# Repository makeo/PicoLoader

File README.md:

# PicoLoader
This is an ODE-based modchip for the Nintendo GameCube to boot homebrew.\
Its price and functionality are very similar to [PicoBoot](https://github.com/webhdx/PicoBoot) but it has multiple advantages.

Join the [Discord server](https://discord.gg/YtA9aU3BKZ) to get support and discuss the mod!

## How does it work?
This mod works by emulating a disk drive during boot, executing a homebrew app, and afterwards re-enabling the disk drive.\
This is achieved using a flex PCB similar to FlippyDrive.
However, it is not a full optical drive emulator and only allows executing small homebrew apps (e.g. [swiss](https://github.com/emukidid/swiss-gc)) from flash just like PicoBoot.
To access files on an SD card, you need an SDGecko, SD2SP2, or similar adapter, which can be purchased separately.

## Features
- Open source
- You can keep the disk drive
- Simple to boot most homebrew apps using an [online converter](https://makeo.github.io/PicoLoader/converter/)
- No permanent modifications to the GameCube
- [3D printed plug](https://github.com/makeo/PicoLoader/raw/refs/heads/main/mount/Drive_PlugV1.1.stl) for installs without a disk drive 
- Easy to remove
- Running Pico at 200Mhz for better compatibility with clone boards

#### Soldered Variant
- Cheap and easy to get components (Raspberry Pi Pico/Pico 2 + Flex PCB + Diode)
- Readily available
- No soldering directly to the GameCube
- Easy soldering
- Alternative install options: [Panasonic Q](https://github.com/makeo/PicoLoader/wiki/4.-Advanced-Section#panasonic-q-install-option), [low-profile](https://github.com/makeo/PicoLoader/wiki/4.-Advanced-Section#low-profile-install-option)

#### Solderless Variant
- No soldering
- Easily replaceable flex PCB
- Pre-programmed with PicoLoader firmware and [Swiss](https://github.com/emukidid/swiss-gc)
> [!TIP]
> You can buy the solderless and normal variant from [store.makstech.io](https://store.makstech.io/).

## Planned Features
*cricked sound*

## Installation & Documentation
> [!IMPORTANT]
> Please follow the [installation instructions](https://makeo.github.io/PicoLoader/) in the wiki.\
> When not following the instructions, there is a chance of breaking the flex PCB during installation.

Get started by looking at the 📖[Wiki](https://github.com/makeo/PicoLoader/wiki/1.-Home)!

## Gallery

<div style="display: flex; gap: 10px; flex-wrap: nowrap; justify-content: center;">

</div>
<div style="display: flex; gap: 10px; flex-wrap: nowrap; justify-content: center;">

</div>

## Special Thanks
- [silversteel](https://github.com/silverstee1) for his help, especially for making the flex PCBs and mounts
- [TeamOffBroadway](https://github.com/OffBroadway) for the amazing idea to use a flex PCB to intercept the drive signals
- [Extrems](https://github.com/Extrems), [emukidid](https://github.com/emukidid) and everyone involved in creating Swiss
- [novenary (9ary)](https://github.com/9ary) for gekkoboot

## Acknowledgements
The source of [gbi.hdr](https://github.com/makeo/PicoLoader/blob/main/picoloader/data/gbi.hdr) and [gbi_disable_ipl.hdr](https://github.com/makeo/PicoLoader/blob/main/picoloader/data/gbi_disable_ipl.hdr) is licensed under GPL-2.0 and available [here](https://github.com/makeo/cubeboot-tools)

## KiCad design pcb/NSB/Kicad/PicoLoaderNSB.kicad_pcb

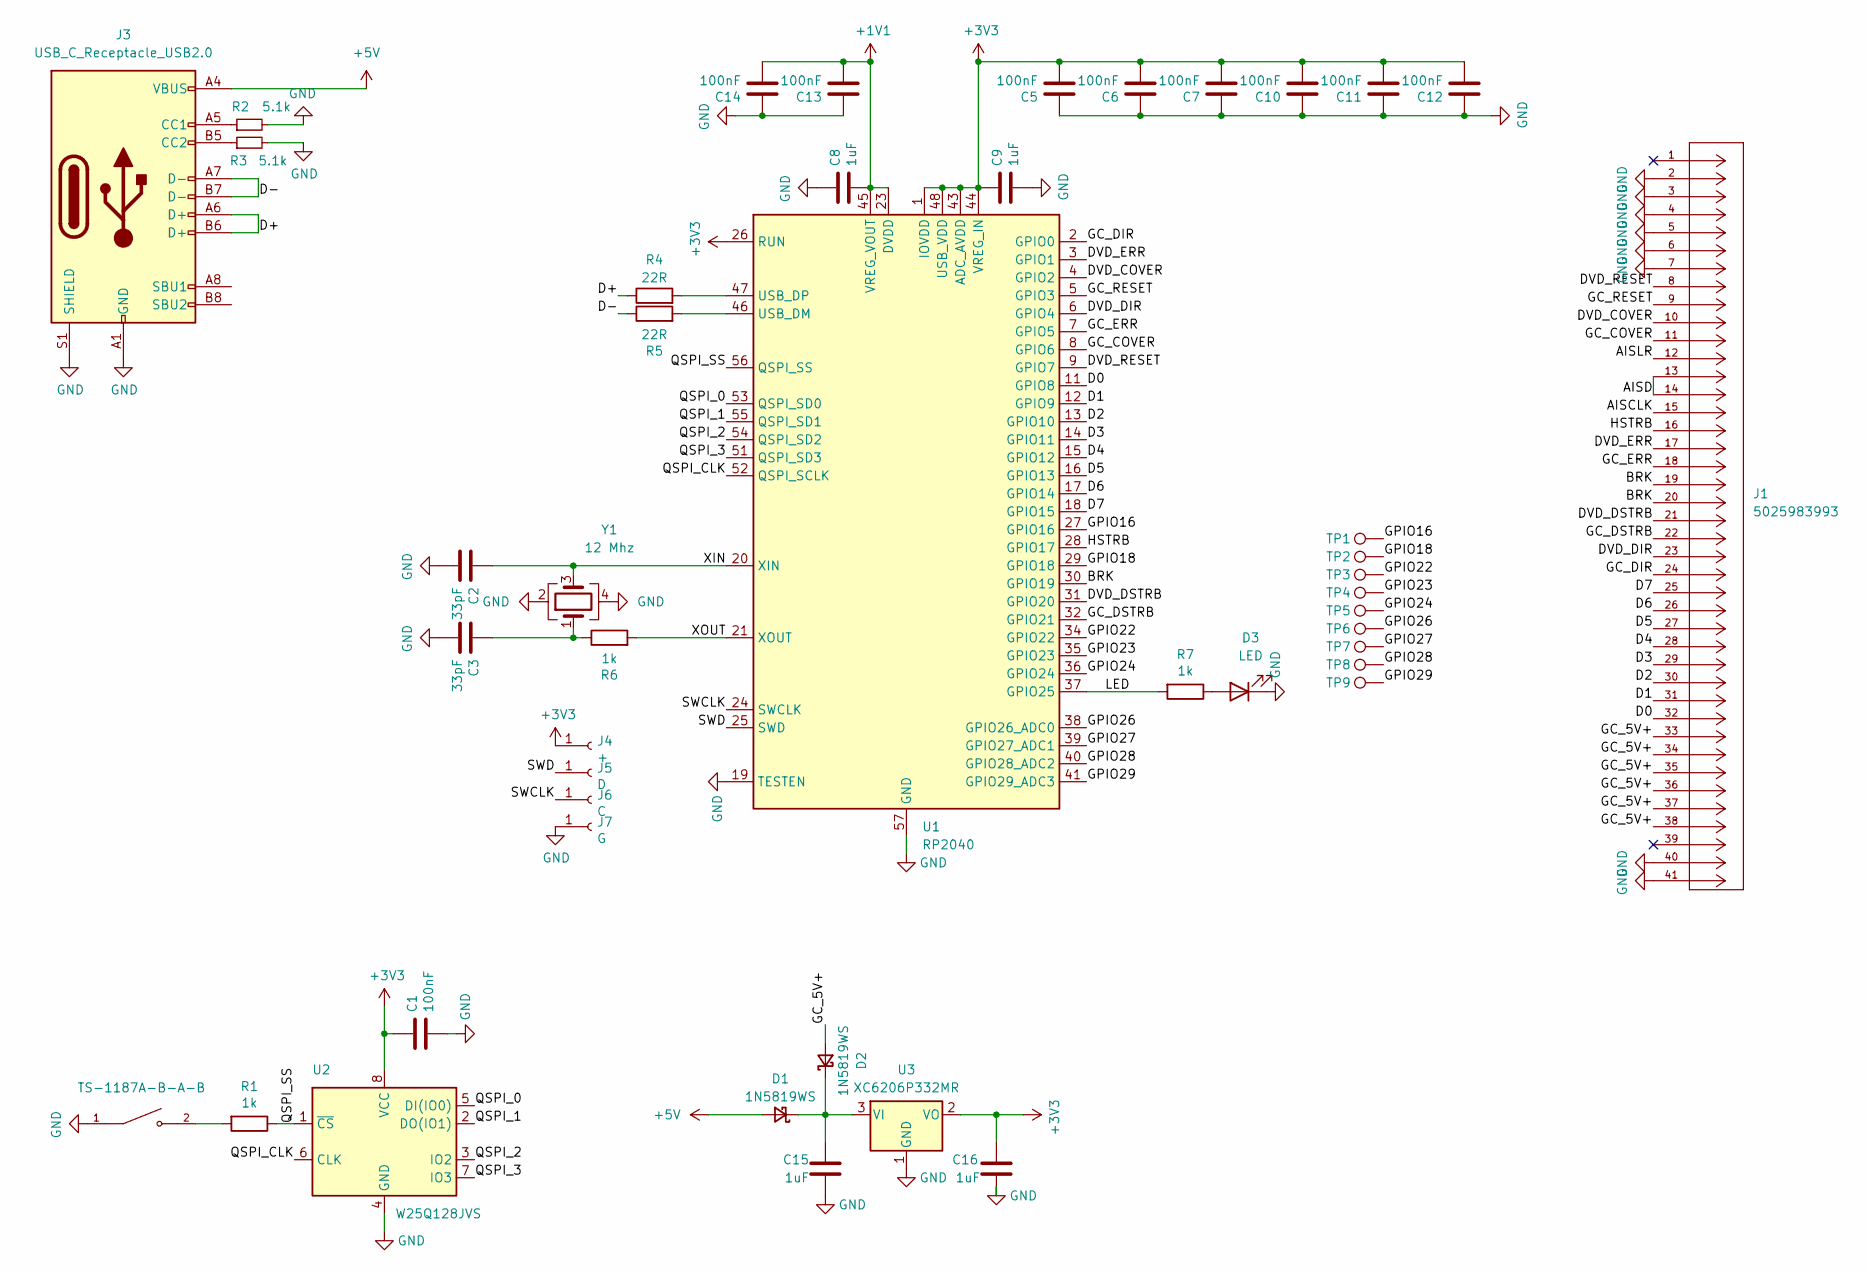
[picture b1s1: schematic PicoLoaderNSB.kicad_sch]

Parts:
C1, C5, C6, C7, C10, C11, C12, C13, C14: 100nF; C_0402_1005Metric; LCSC C1525
C2, C3: 33pF; C_0402_1005Metric; LCSC C1562
C8, C9, C15, C16: 1uF; C_0402_1005Metric; LCSC C52923
D1, D2: 1N5819WS; D_SOD-323; LCSC C191023
D3: LED; LED_0805_2012Metric; LCSC C2297
J1: 5025983993; CONN_502598-3993_MOL; MANUFACTURER_PART_NUMBER 5025983993; LCSC C505359
J3: USB_C_Receptacle_USB2.0; USB_C_Receptacle_Palconn_UTC16-G; LCSC C165948
J4: +; TestPoint_Pad_D1.0mm
J5: D; TestPoint_Pad_D1.0mm
J6: C; TestPoint_Pad_D1.0mm
J7: G; TestPoint_Pad_D1.0mm
R1, R6, R7: 1k; R_0402_1005Metric; LCSC C11702
R2, R3: 5.1k; R_0402_1005Metric; LCSC C25905
R4, R5: 22R; R_0402_1005Metric; LCSC C25092
S1: TS-1187A-B-A-B; PARTREV A0; LCSC C318884
TP1, TP2, TP3, TP4, TP5, TP6, TP7, TP8, TP9: TestPoint; TestPoint_Pad_D1.0mm
U1: RP2040; QFN-56-1EP_7x7mm_P0.4mm_EP3.2x3.2mm; LCSC C2040
U2: W25Q128JVS; SOIC-8_5.3x5.3mm_P1.27mm; LCSC C97521
U3: XC6206P332MR; SOT-23; LCSC C5446
Y1: 12 Mhz; Crystal_SMD_3225-4Pin_3.2x2.5mm; LCSC C9002

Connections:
+1V1: C8.2, C13.2, C14.2, U1.23 (DVDD), U1.45 (VREG_VOUT), U1.50 (DVDD)
+3V3: C1.1, C5.2, C6.2, C7.2, C9.1, C10.2, C11.2, C12.2, C16.1, J4.1, U1.1 (IOVDD), U1.10 (IOVDD), U1.22 (IOVDD), U1.26 (RUN), U1.33 (IOVDD), U1.42 (IOVDD), U1.43 (ADC_AVDD), U1.44 (VREG_IN), U1.48 (USB_VDD), U1.49 (IOVDD), U2.8 (VCC), U3.2 (VO)
+5V: D1.2 (A), J3.A4 (VBUS), J3.A9 (VBUS), J3.B4 (VBUS), J3.B9 (VBUS)
/AISCLK: J1.15
/AISD: J1.13, J1.14
/AISLR: J1.12
/BRK: J1.19, J1.20, U1.30 (GPIO19)
/D0: J1.32, U1.11 (GPIO8)
/D1: J1.31, U1.12 (GPIO9)
/D2: J1.30, U1.13 (GPIO10)
/D3: J1.29, U1.14 (GPIO11)
/D4: J1.28, U1.15 (GPIO12)
/D5: J1.27, U1.16 (GPIO13)
/D6: J1.26, U1.17 (GPIO14)
/D7: J1.25, U1.18 (GPIO15)
/D+: J3.A6 (D+), J3.B6 (D+), R4.1
/D-: J3.A7 (D-), J3.B7 (D-), R5.1
/DVD_COVER: J1.10, U1.4 (GPIO2)
/DVD_DIR: J1.23, U1.6 (GPIO4)
/DVD_DSTRB: J1.21, U1.31 (GPIO20)
/DVD_ERR: J1.17, U1.3 (GPIO1)
/DVD_RESET: J1.8, U1.9 (GPIO7)
/GC_5V+: D2.2 (A), J1.33, J1.34, J1.35, J1.36, J1.37, J1.38
/GC_COVER: J1.11, U1.8 (GPIO6)
/GC_DIR: J1.24, U1.2 (GPIO0)
/GC_DSTRB: J1.22, U1.32 (GPIO21)
/GC_ERR: J1.18, U1.7 (GPIO5)
/GC_RESET: J1.9, U1.5 (GPIO3)
/GPIO16: TP1.1, U1.27 (GPIO16)
/GPIO18: TP2.1, U1.29 (GPIO18)
/GPIO22: TP3.1, U1.34 (GPIO22)
/GPIO23: TP4.1, U1.35 (GPIO23)
/GPIO24: TP5.1, U1.36 (GPIO24)
/GPIO26: TP6.1, U1.38 (GPIO26_ADC0)
/GPIO27: TP7.1, U1.39 (GPIO27_ADC1)
/GPIO28: TP8.1, U1.40 (GPIO28_ADC2)
/GPIO29: TP9.1, U1.41 (GPIO29_ADC3)
/HSTRB: J1.16, U1.28 (GPIO17)
/LED: R7.2, U1.37 (GPIO25)
/QSPI_0: U1.53 (QSPI_SD0), U2.5 (DI(IO0))
/QSPI_1: U1.55 (QSPI_SD1), U2.2 (DO(IO1))
/QSPI_2: U1.54 (QSPI_SD2), U2.3 (IO2)
/QSPI_3: U1.51 (QSPI_SD3), U2.7 (IO3)
/QSPI_CLK: U1.52 (QSPI_SCLK), U2.6 (CLK)
/QSPI_SS: R1.1, U1.56 (QSPI_SS), U2.1 (~CS)
/SWCLK: J6.1, U1.24 (SWCLK)
/SWD: J5.1, U1.25 (SWD)
/XIN: C2.1, U1.20 (XIN), Y1.3
/XOUT: R6.2, U1.21 (XOUT)
GND: C1.2, C2.2, C3.2, C5.1, C6.1, C7.1, C8.1, C9.2, C10.1, C11.1, C12.1, C13.1, C14.1, C15.2, C16.2, D3.1 (K), J1.2, J1.3, J1.4, J1.5, J1.6, J1.7, J1.40, J1.41, J3.A1 (GND), J3.A12 (GND), J3.B1 (GND), J3.B12 (GND), J3.S1 (SHIELD), J7.1, R2.2, R3.2, S1.1, U1.19 (TESTEN), U1.57 (GND), U2.4 (GND), U3.1 (GND), Y1.2, Y1.4
unnamed: C3.1, R6.1, Y1.1
unnamed: C15.1, D1.1 (K), D2.1 (K), U3.3 (VI)
unnamed: D3.2 (A), R7.1
unnamed: J3.A5 (CC1), R2.1
unnamed: J3.B5 (CC2), R3.1
unnamed: R1.2, S1.2
unnamed: R5.2, U1.46 (USB_DM)
unnamed: R4.2, U1.47 (USB_DP)

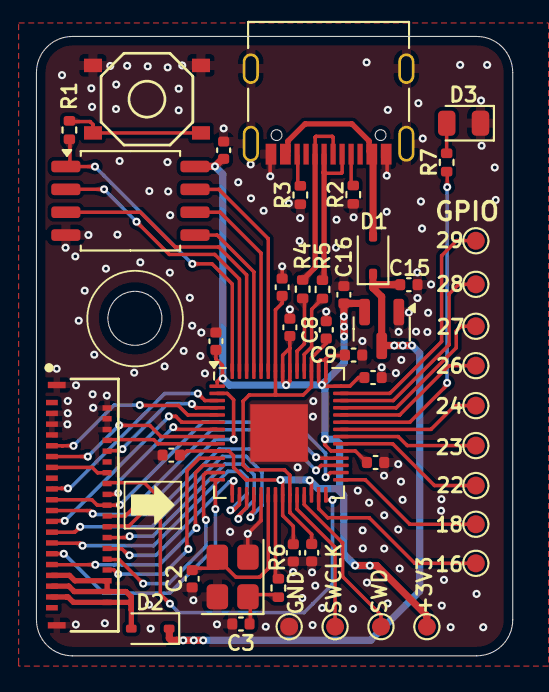
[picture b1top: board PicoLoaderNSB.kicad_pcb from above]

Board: 2 copper layers, 26.5 x 34.4 mm, 45 parts (0 on the bottom side), 56 nets.

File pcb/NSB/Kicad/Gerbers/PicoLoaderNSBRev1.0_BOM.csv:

Designator,Footprint,Quantity,Value,LCSC Part #
"C1, C10, C11, C12, C13, C14, C5, C6, C7",0402,9,100nF,C1525
"C15, C16, C8, C9",0402,4,1uF,C52923
"C2, C3",0402,2,33pF,C1562
"D1, D2",D_SOD-323,2,1N5819WS,C191023
D3,0805,1,LED,C2297
J1,CONN_502598-3993_MOL,1,5025983993,C505359
J3,USB_C_Receptacle_Palconn_UTC16-G,1,USB_C_Receptacle_USB2.0,C165948
J4,TestPoint_Pad_D1.0mm,1,+,
J5,TestPoint_Pad_D1.0mm,1,D,
J6,TestPoint_Pad_D1.0mm,1,C,
J7,TestPoint_Pad_D1.0mm,1,G,
"R1, R6, R7",0402,3,1k,C11702
"R2, R3",0402,2,5.1k,C25905
"R4, R5",0402,2,22R,C25092
S1,TS-1187A-B-A-B,1,TS-1187A-B-A-B,C318884
"TP1, TP2, TP3, TP4, TP5, TP6, TP7, TP8, TP9",TestPoint_Pad_D1.0mm,9,TestPoint,
U1,QFN-56-1EP_7x7mm_P0.4mm_EP3.2x3.2mm,1,RP2040,C2040
U2,SOIC-8_5.3x5.3mm_P1.27mm,1,W25Q128JVS,C97521
U3,SOT-23,1,XC6206P332MR,C5446
Y1,Crystal_SMD_3225-4Pin_3.2x2.5mm,1,12 Mhz,C9002

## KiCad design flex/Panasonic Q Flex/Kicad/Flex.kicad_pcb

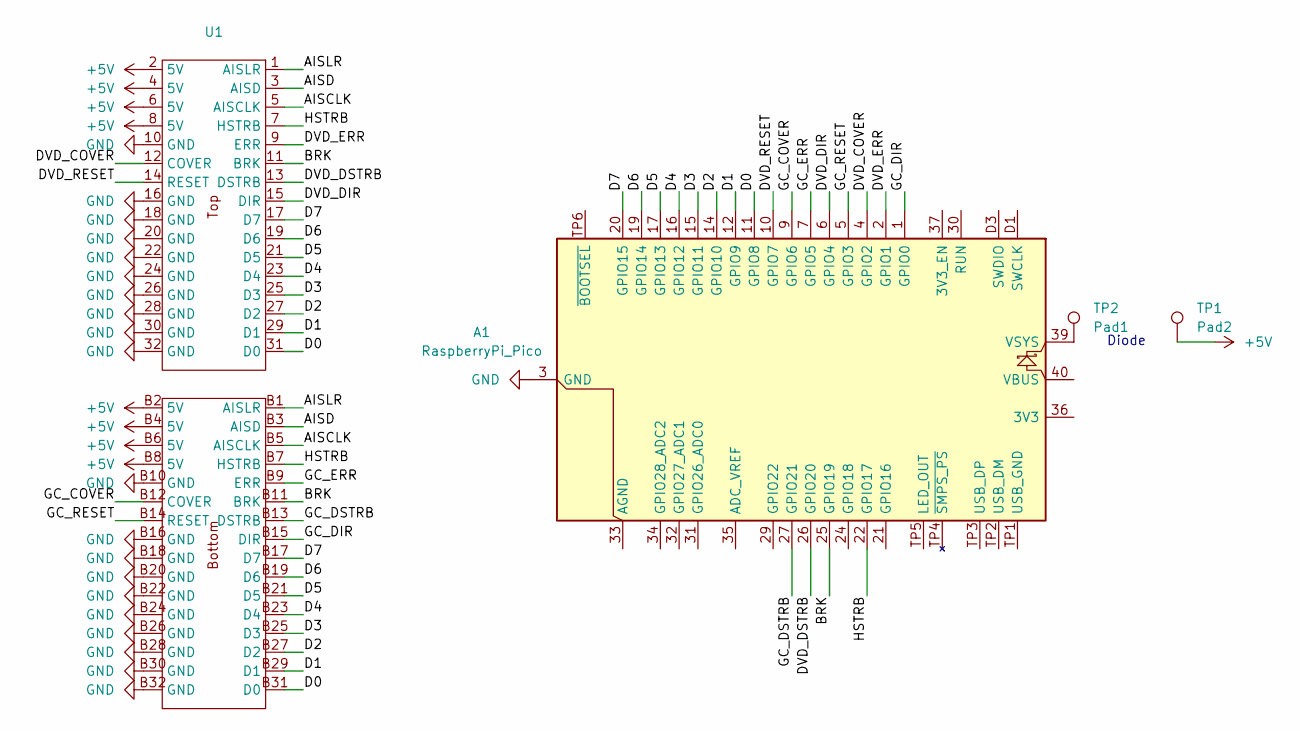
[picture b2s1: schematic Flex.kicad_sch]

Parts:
A1: RaspberryPi_Pico; RaspberryPi_Pico_SMD
TP1: Pad2; TestPoint_Pad_2.5x2.5mm
TP2: Pad1; TestPoint_Pad_2.5x2.5mm
U1: DVDCN_FLEX_PADS

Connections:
+5V: TP1.1, U1.2 (5V), U1.4 (5V), U1.6 (5V), U1.8 (5V), U1.B2 (5V), U1.B4 (5V), U1.B6 (5V), U1.B8 (5V)
/AISCLK: U1.5 (AISCLK), U1.B5 (AISCLK)
/AISD: U1.3 (AISD), U1.B3 (AISD)
/AISLR: U1.1 (AISLR), U1.B1 (AISLR)
/BRK: A1.25 (GPIO19), U1.11 (BRK), U1.B11 (BRK)
/D0: A1.11 (GPIO8), U1.31 (D0), U1.B31 (D0)
/D1: A1.12 (GPIO9), U1.29 (D1), U1.B29 (D1)
/D2: A1.14 (GPIO10), U1.27 (D2), U1.B27 (D2)
/D3: A1.15 (GPIO11), U1.25 (D3), U1.B25 (D3)
/D4: A1.16 (GPIO12), U1.23 (D4), U1.B23 (D4)
/D5: A1.17 (GPIO13), U1.21 (D5), U1.B21 (D5)
/D6: A1.19 (GPIO14), U1.19 (D6), U1.B19 (D6)
/D7: A1.20 (GPIO15), U1.17 (D7), U1.B17 (D7)
/DVD_COVER: A1.4 (GPIO2), U1.12 (COVER)
/DVD_DIR: A1.6 (GPIO4), U1.15 (DIR)
/DVD_DSTRB: A1.26 (GPIO20), U1.13 (DSTRB)
/DVD_ERR: A1.2 (GPIO1), U1.9 (ERR)
/DVD_RESET: A1.10 (GPIO7), U1.14 (RESET)
/GC_COVER: A1.9 (GPIO6), U1.B12 (COVER)
/GC_DIR: A1.1 (GPIO0), U1.B15 (DIR)
/GC_DSTRB: A1.27 (GPIO21), U1.B13 (DSTRB)
/GC_ERR: A1.7 (GPIO5), U1.B9 (ERR)
/GC_RESET: A1.5 (GPIO3), U1.B14 (RESET)
/HSTRB: A1.22 (GPIO17), U1.7 (HSTRB), U1.B7 (HSTRB)
GND: A1.3 (GND), A1.8 (GND), A1.13 (GND), A1.18 (GND), A1.23 (GND), A1.28 (GND), A1.38 (GND), A1.D2 (GND), U1.10 (GND), U1.16 (GND), U1.18 (GND), U1.20 (GND), U1.22 (GND), U1.24 (GND), U1.26 (GND), U1.28 (GND), U1.30 (GND), U1.32 (GND), U1.B10 (GND), U1.B16 (GND), U1.B18 (GND), U1.B20 (GND), U1.B22 (GND), U1.B24 (GND), U1.B26 (GND), U1.B28 (GND), U1.B30 (GND), U1.B32 (GND)
unnamed: A1.39 (VSYS), TP2.1

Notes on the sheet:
Diode

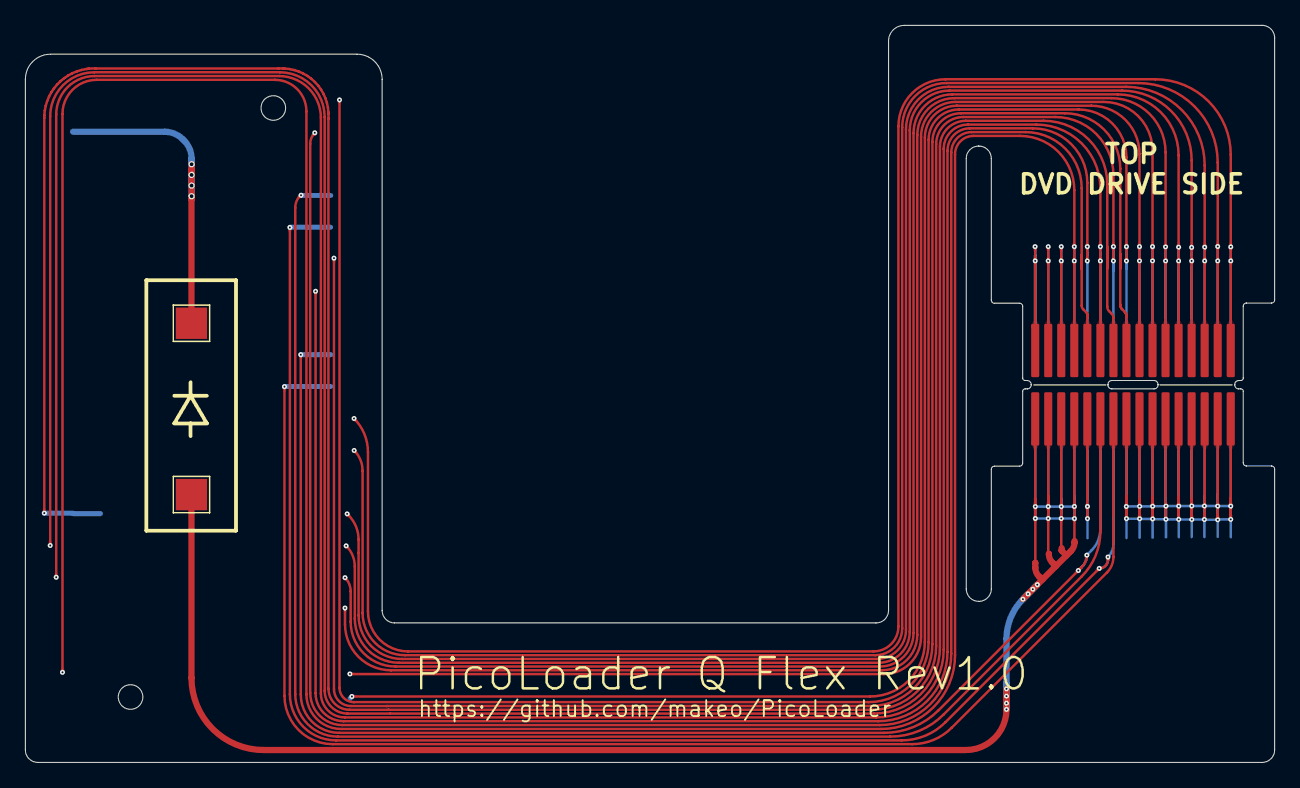
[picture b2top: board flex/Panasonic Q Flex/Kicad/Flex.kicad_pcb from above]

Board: 2 copper layers, 99.7 x 58.8 mm, 4 parts (1 on the bottom side), 26 nets.

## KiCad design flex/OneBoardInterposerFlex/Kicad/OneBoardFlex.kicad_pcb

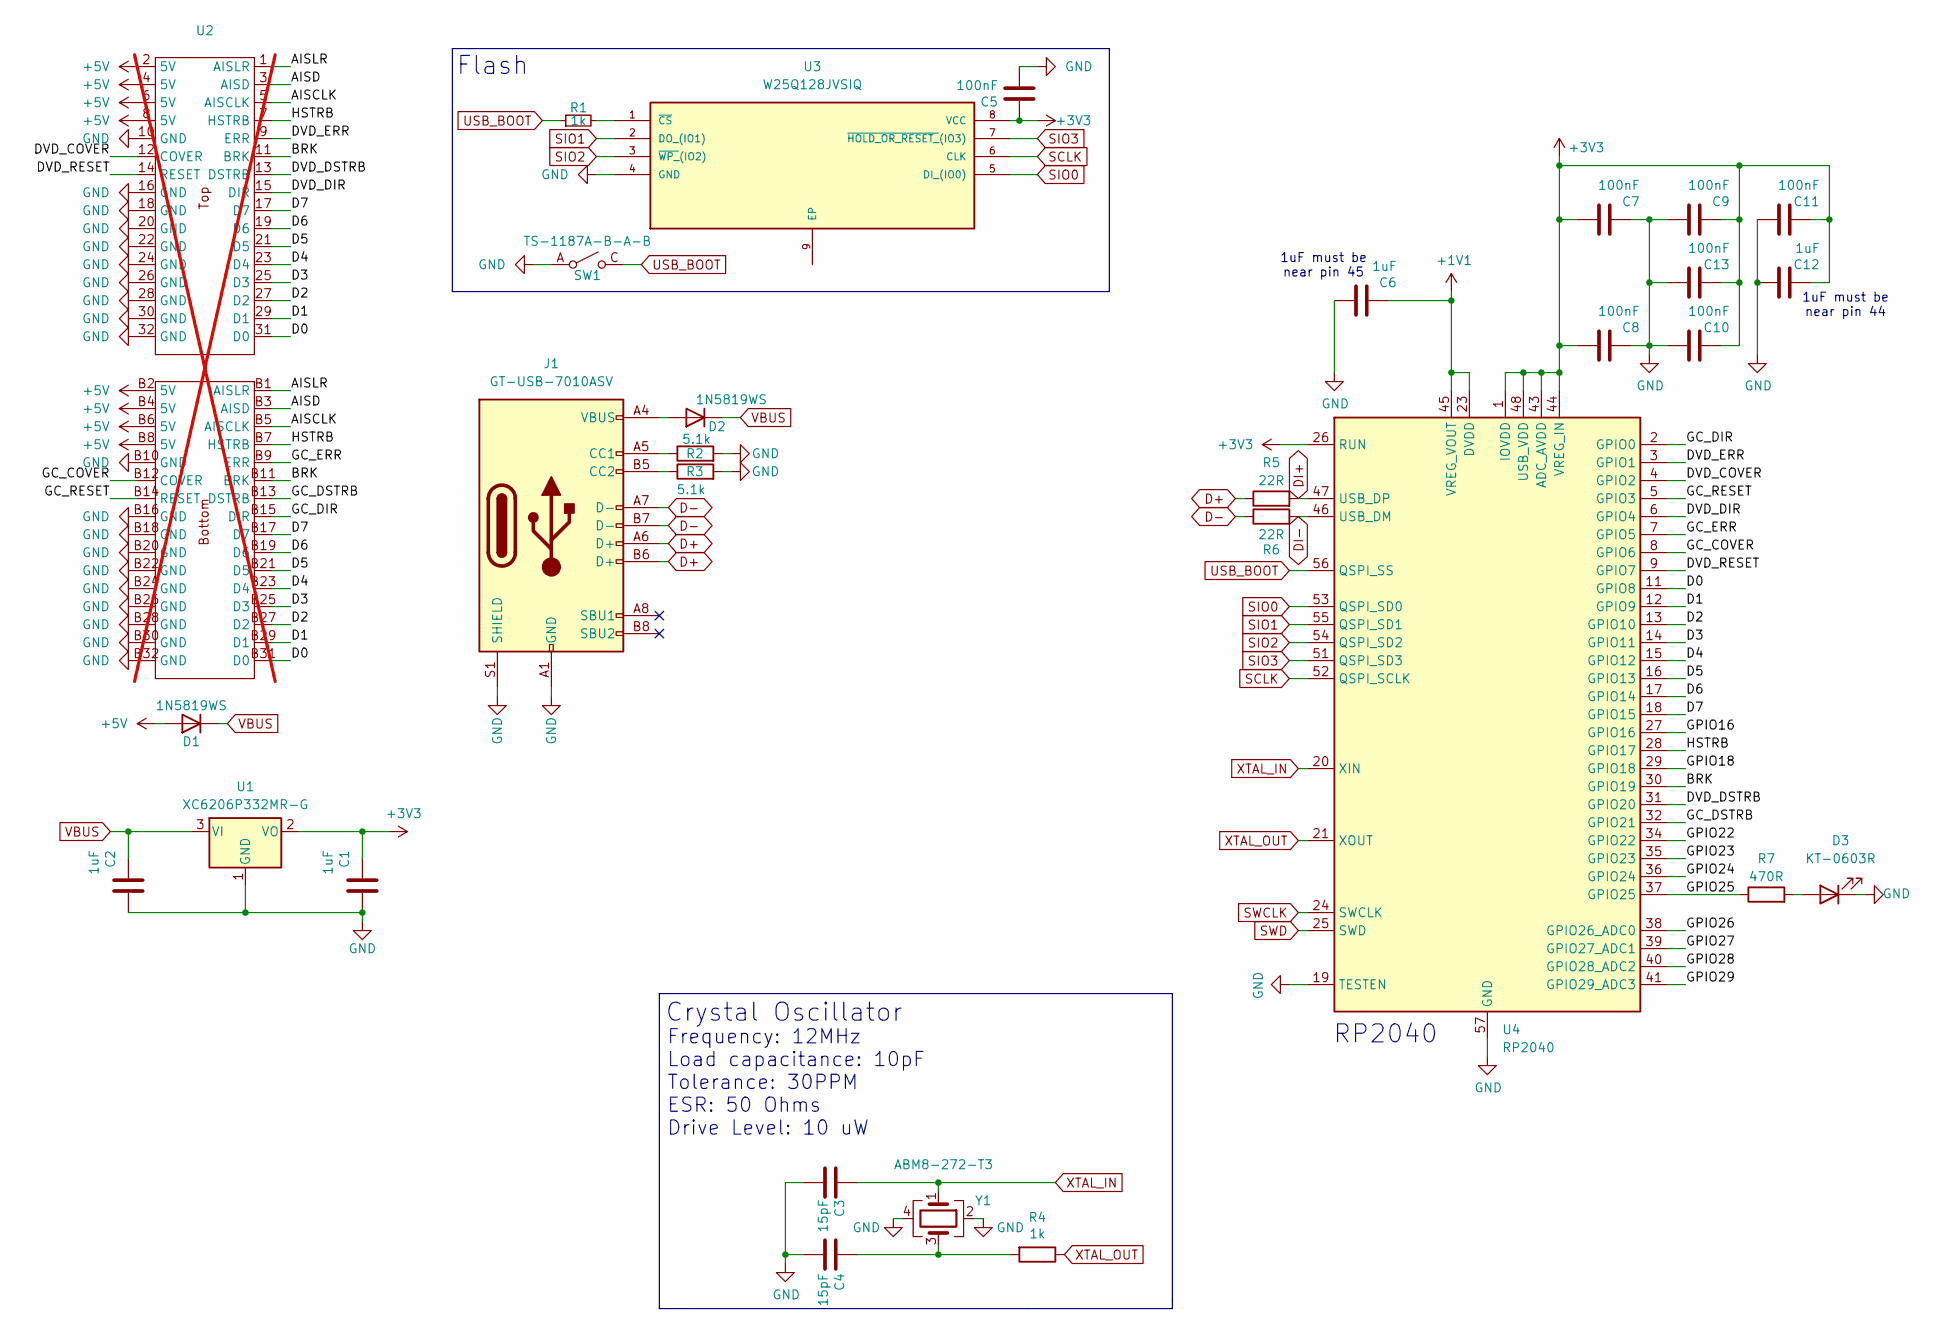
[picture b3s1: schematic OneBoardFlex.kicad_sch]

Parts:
C1, C2, C6, C12: 1uF; C_0402_1005Metric; MPN GRM033R60J105KEA2D; JLCPN C52923
C3, C4: 15pF; C_0402_1005Metric; MPN CC0402FRNPO9BN150; JLCPN C1548
C5, C7, C8, C9, C10, C11, C13: 100nF; C_0402_1005Metric; MPN CL03A104KQ3NNNC; JLCPN C1525
D1, D2: 1N5819WS; D_SOD-323; MPN CUS08F30,H3F; JLCPN C191023
D3: KT-0603R; LED_0603_1608Metric; JLCPN C2286
J1: GT-USB-7010ASV; USB_C_Receptacle_GT-USB-7010; JLCPN C2988369
R1, R4: 1k; R_0402_1005Metric; MPN RC0201FR-071KL; JLCPN C11702
R2, R3: 5.1k; R_0402_1005Metric; MPN RC0201FR-075K1L; JLCPN C25905
R5, R6: 22R; R_0402_1005Metric; MPN RC0201FR-0727RL; JLCPN C25092
R7: 470R; R_0402_1005Metric; JLCPN C25117
SW1: TS-1187A-B-A-B; TS-1187A-C-E-B; MPN TS-1187A-C-E-B; JLCPN C318884
U1: XC6206P332MR-G; SOT-23-3; JLCPN C5446
U2: DVDCN_FLEX_PADS; not fitted
U3: W25Q128JVSIQ; SOIC-8_5.3x5.3mm_P1.27mm; JLCPN C97521
U4: RP2040; QFN-56-1EP_7x7mm_P0.4mm_EP3.2x3.2mm; MPN RP2040; JLCPN C2040
Y1: ABM8-272-T3; Crystal_SMD_3225-4Pin_3.2x2.5mm; MPN ABM8-272-T3; JLCPN C20625731

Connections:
+1V1: C6.2, U4.23 (DVDD), U4.45 (VREG_VOUT), U4.50 (DVDD)
+3V3: C1.2, C5.1, C7.1, C8.1, C9.2, C10.2, C11.2, C12.2, C13.2, U1.2 (VO), U3.8 (VCC), U4.1 (IOVDD), U4.10 (IOVDD), U4.22 (IOVDD), U4.26 (RUN), U4.33 (IOVDD), U4.42 (IOVDD), U4.43 (ADC_AVDD), U4.44 (VREG_IN), U4.48 (USB_VDD), U4.49 (IOVDD)
+5V: D1.2 (A), U2.2 (5V), U2.4 (5V), U2.6 (5V), U2.8 (5V), U2.B2 (5V), U2.B4 (5V), U2.B6 (5V), U2.B8 (5V)
/AISCLK: U2.5 (AISCLK), U2.B5 (AISCLK)
/AISD: U2.3 (AISD), U2.B3 (AISD)
/AISLR: U2.1 (AISLR), U2.B1 (AISLR)
/BRK: U2.11 (BRK), U2.B11 (BRK), U4.30 (GPIO19)
/D0: U2.31 (D0), U2.B31 (D0), U4.11 (GPIO8)
/D1: U2.29 (D1), U2.B29 (D1), U4.12 (GPIO9)
/D2: U2.27 (D2), U2.B27 (D2), U4.13 (GPIO10)
/D3: U2.25 (D3), U2.B25 (D3), U4.14 (GPIO11)
/D4: U2.23 (D4), U2.B23 (D4), U4.15 (GPIO12)
/D5: U2.21 (D5), U2.B21 (D5), U4.16 (GPIO13)
/D6: U2.19 (D6), U2.B19 (D6), U4.17 (GPIO14)
/D7: U2.17 (D7), U2.B17 (D7), U4.18 (GPIO15)
/DVD_COVER: U2.12 (COVER), U4.4 (GPIO2)
/DVD_DIR: U2.15 (DIR), U4.6 (GPIO4)
/DVD_DSTRB: U2.13 (DSTRB), U4.31 (GPIO20)
/DVD_ERR: U2.9 (ERR), U4.3 (GPIO1)
/DVD_RESET: U2.14 (RESET), U4.9 (GPIO7)
/GC_COVER: U2.B12 (COVER), U4.8 (GPIO6)
/GC_DIR: U2.B15 (DIR), U4.2 (GPIO0)
/GC_DSTRB: U2.B13 (DSTRB), U4.32 (GPIO21)
/GC_ERR: U2.B9 (ERR), U4.7 (GPIO5)
/GC_RESET: U2.B14 (RESET), U4.5 (GPIO3)
/GPIO16: U4.27 (GPIO16)
/GPIO18: U4.29 (GPIO18)
/GPIO22: U4.34 (GPIO22)
/GPIO23: U4.35 (GPIO23)
/GPIO24: U4.36 (GPIO24)
/GPIO25: R7.1, U4.37 (GPIO25)
/GPIO26: U4.38 (GPIO26_ADC0)
/GPIO27: U4.39 (GPIO27_ADC1)
/GPIO28: U4.40 (GPIO28_ADC2)
/GPIO29: U4.41 (GPIO29_ADC3)
/HSTRB: U2.7 (HSTRB), U2.B7 (HSTRB), U4.28 (GPIO17)
D+: J1.A6 (D+), J1.B6 (D+), R5.1
D-: J1.A7 (D-), J1.B7 (D-), R6.1
DI+: R5.2, U4.47 (USB_DP)
DI-: R6.2, U4.46 (USB_DM)
GND: C1.1, C2.1, C3.2, C4.2, C5.2, C6.1, C7.2, C8.2, C9.1, C10.1, C11.1, C12.1, C13.1, D3.1 (K), J1.A1 (GND), J1.A12 (GND), J1.B1 (GND), J1.B12 (GND), J1.S1 (SHIELD), R2.2, R3.2, SW1.A, SW1.B, U1.1 (GND), U2.10 (GND), U2.16 (GND), U2.18 (GND), U2.20 (GND), U2.22 (GND), U2.24 (GND), U2.26 (GND), U2.28 (GND), U2.30 (GND), U2.32 (GND), U2.B10 (GND), U2.B16 (GND), U2.B18 (GND), U2.B20 (GND), U2.B22 (GND), U2.B24 (GND), U2.B26 (GND), U2.B28 (GND), U2.B30 (GND), U2.B32 (GND), U3.4 (GND), U4.19 (TESTEN), U4.57 (GND), Y1.2, Y1.4
unnamed: C4.1, R4.2, Y1.3
unnamed: D2.2 (A), J1.A4 (VBUS), J1.A9 (VBUS), J1.B4 (VBUS), J1.B9 (VBUS)
unnamed: D3.2 (A), R7.2
unnamed: J1.A5 (CC1), R2.1
unnamed: J1.B5 (CC2), R3.1
unnamed: R1.2, U3.1 (~CS)
SCLK: U3.6 (CLK), U4.52 (QSPI_SCLK)
SIO0: U3.5 (DI_(IO0)), U4.53 (QSPI_SD0)
SIO1: U3.2 (DO_(IO1)), U4.55 (QSPI_SD1)
SIO2: U3.3 (~WP_(IO2)), U4.54 (QSPI_SD2)
SIO3: U3.7 (~HOLD_OR_RESET_(IO3)), U4.51 (QSPI_SD3)
SWCLK: U4.24 (SWCLK)
SWD: U4.25 (SWD)
USB_BOOT: R1.1, SW1.C, SW1.D, U4.56 (QSPI_SS)
VBUS: C2.2, D1.1 (K), D2.1 (K), U1.3 (VI)
XTAL_IN: C3.1, U4.20 (XIN), Y1.1
XTAL_OUT: R4.1, U4.21 (XOUT)

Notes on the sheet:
1uF must be near pin 44
Crystal Oscillator
Flash
1uF must be near pin 45
RP2040
Frequency: 12MHz Load capacitance: 10pF Tolerance: 30PPM ESR: 50 Ohms Drive Level: 10 uW

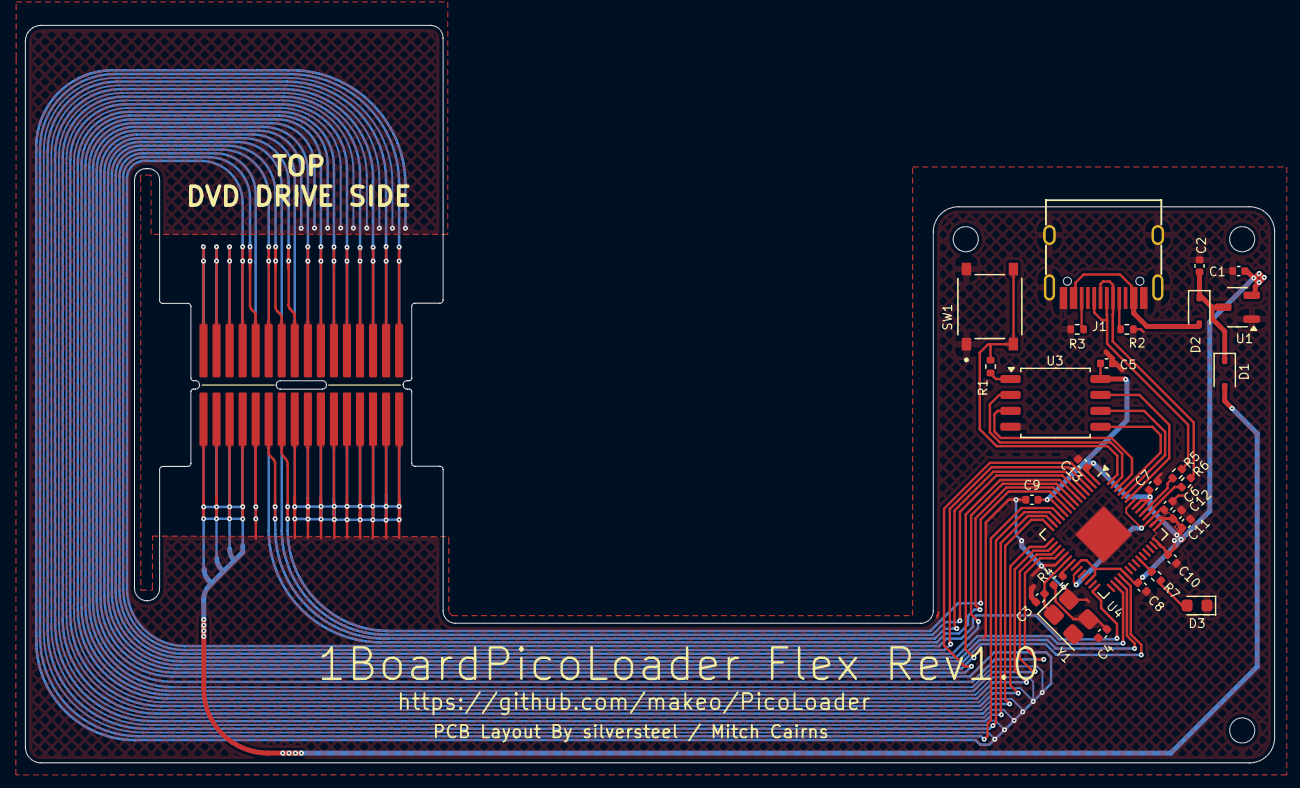
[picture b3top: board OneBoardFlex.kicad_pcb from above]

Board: 2 copper layers, 99.6 x 58.8 mm, 30 parts (0 on the bottom side), 47 nets.

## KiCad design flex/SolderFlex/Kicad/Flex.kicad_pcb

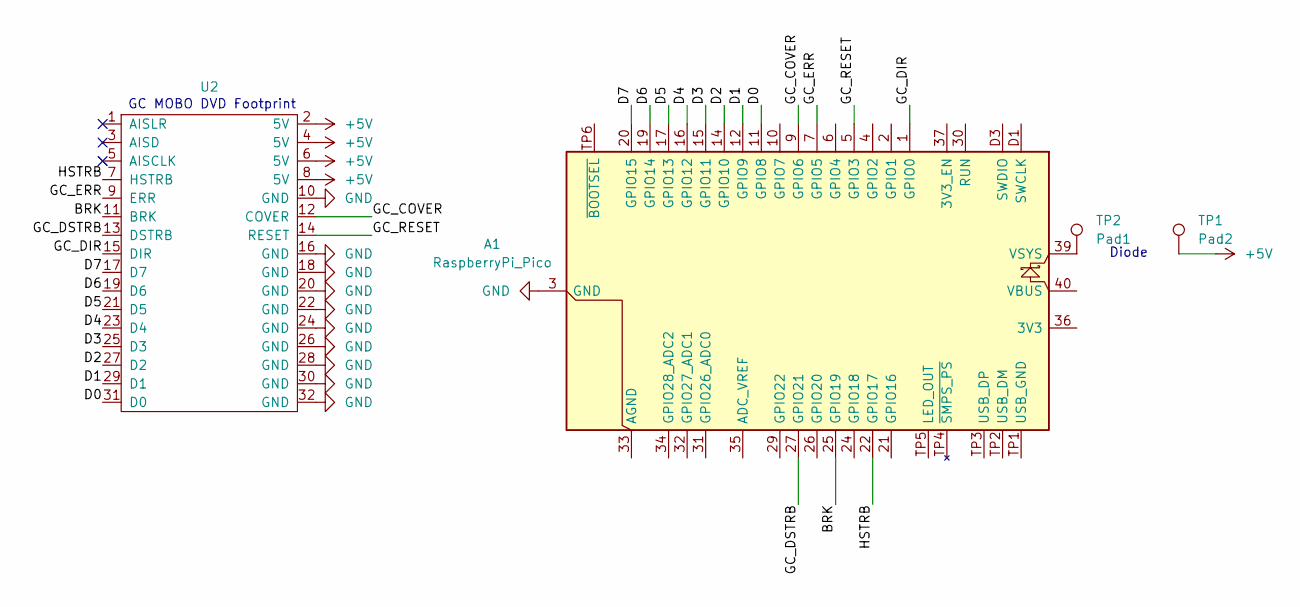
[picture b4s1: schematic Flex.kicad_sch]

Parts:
A1: RaspberryPi_Pico; RaspberryPi_Pico_SMD
TP1: Pad2; TestPoint_Pad_2.5x2.5mm
TP2: Pad1; TestPoint_Pad_2.5x2.5mm
U2: GC_MOBO_DVD_CN

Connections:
+5V: TP1.1, U2.2 (5V), U2.4 (5V), U2.6 (5V), U2.8 (5V)
/BRK: A1.25 (GPIO19), U2.11 (BRK)
/D0: A1.11 (GPIO8), U2.31 (D0)
/D1: A1.12 (GPIO9), U2.29 (D1)
/D2: A1.14 (GPIO10), U2.27 (D2)
/D3: A1.15 (GPIO11), U2.25 (D3)
/D4: A1.16 (GPIO12), U2.23 (D4)
/D5: A1.17 (GPIO13), U2.21 (D5)
/D6: A1.19 (GPIO14), U2.19 (D6)
/D7: A1.20 (GPIO15), U2.17 (D7)
/GC_COVER: A1.9 (GPIO6), U2.12 (COVER)
/GC_DIR: A1.1 (GPIO0), U2.15 (DIR)
/GC_DSTRB: A1.27 (GPIO21), U2.13 (DSTRB)
/GC_ERR: A1.7 (GPIO5), U2.9 (ERR)
/GC_RESET: A1.5 (GPIO3), U2.14 (RESET)
/HSTRB: A1.22 (GPIO17), U2.7 (HSTRB)
GND: A1.3 (GND), A1.8 (GND), A1.13 (GND), A1.18 (GND), A1.23 (GND), A1.28 (GND), A1.38 (GND), A1.D2 (GND), U2.10 (GND), U2.16 (GND), U2.18 (GND), U2.20 (GND), U2.22 (GND), U2.24 (GND), U2.26 (GND), U2.28 (GND), U2.30 (GND), U2.32 (GND)
unnamed: A1.39 (VSYS), TP2.1

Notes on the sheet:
GC MOBO DVD Footprint
Diode

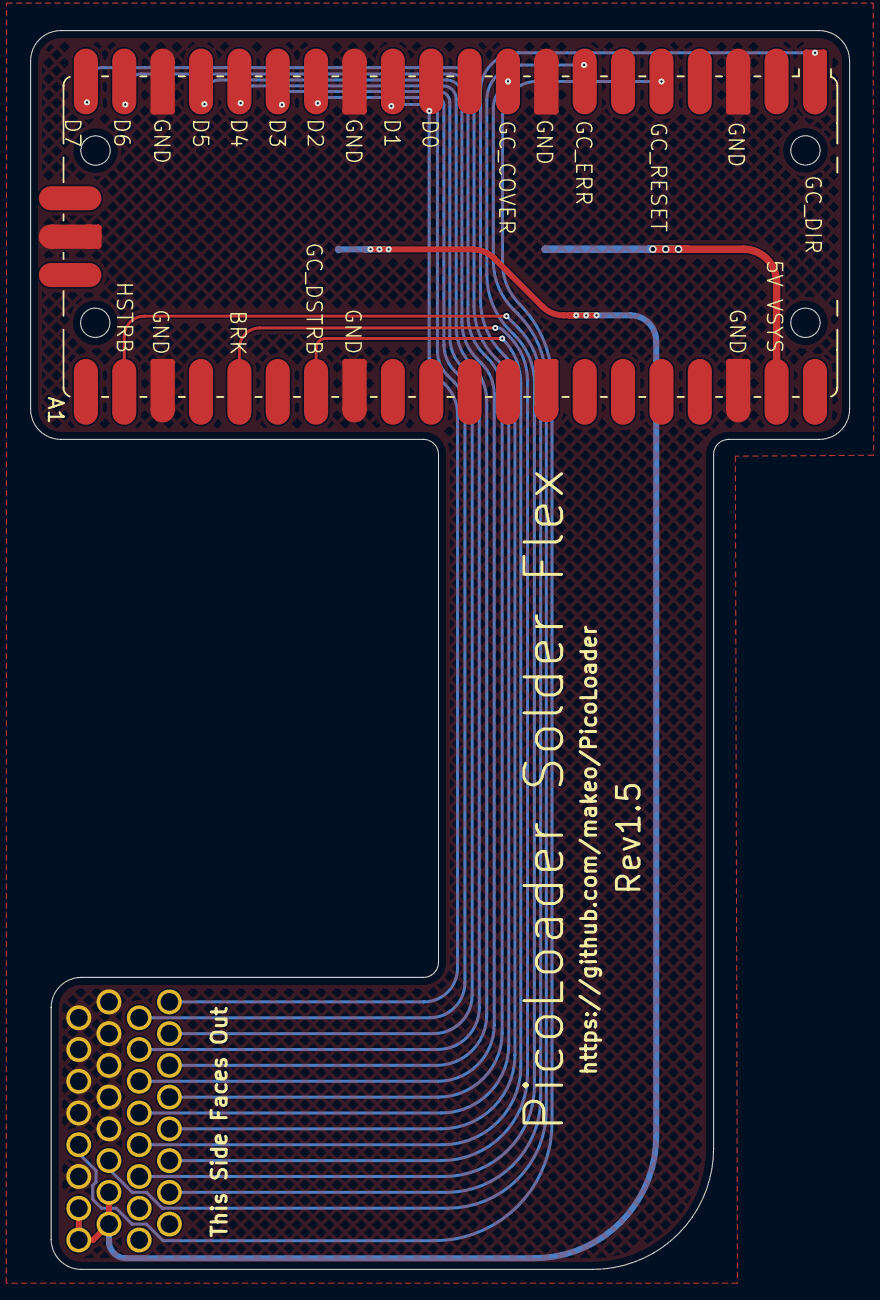
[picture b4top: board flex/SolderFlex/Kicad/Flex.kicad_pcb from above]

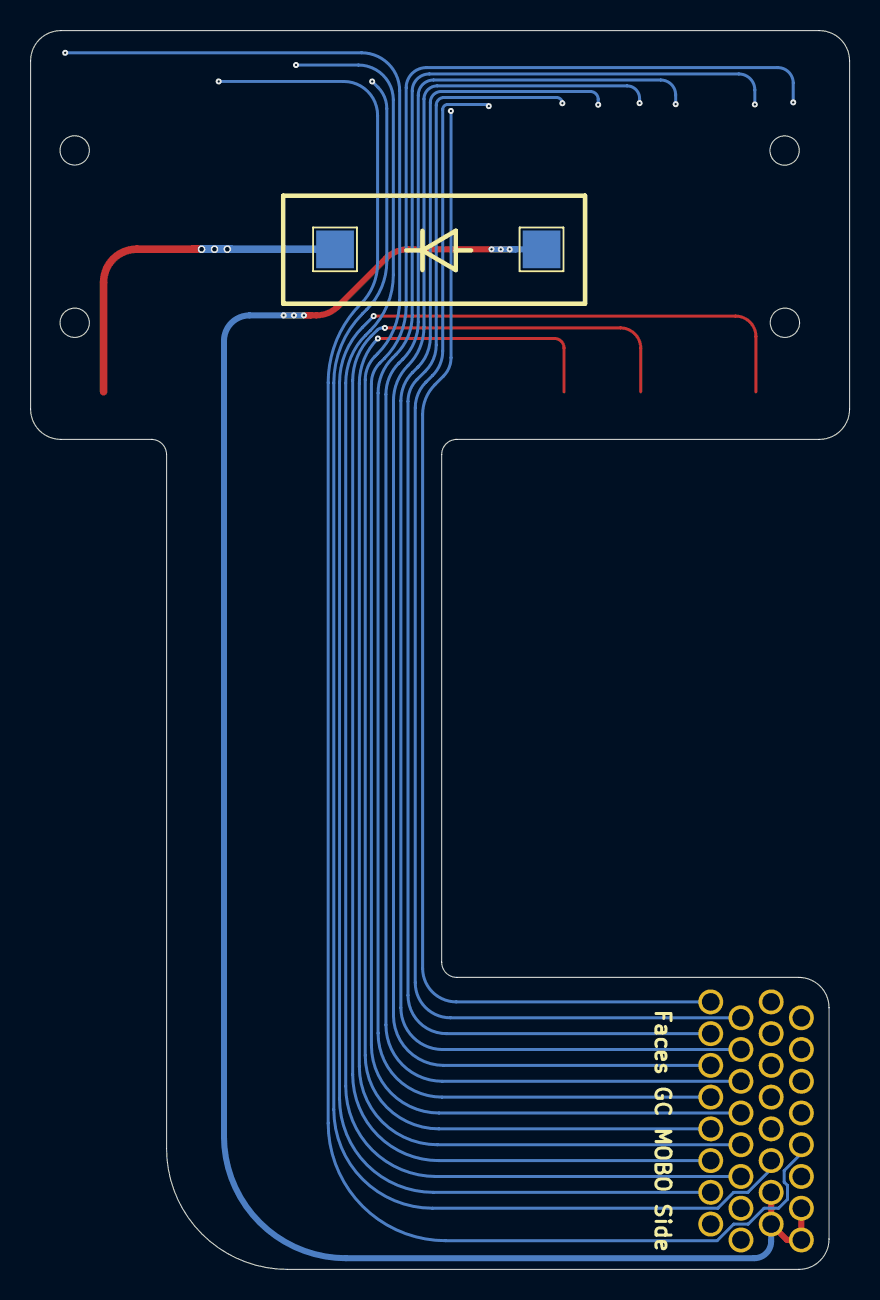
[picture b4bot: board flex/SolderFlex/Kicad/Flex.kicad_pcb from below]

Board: 2 copper layers, 54.2 x 82.0 mm, 4 parts (3 on the bottom side), 18 nets.

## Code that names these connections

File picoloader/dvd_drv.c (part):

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    dvd_drv_init_gpios();

    // hold drive in reset and keep dir low
    gpio_set_outover(pin_dvd_reset, GPIO_OVERRIDE_LOW);
    gpio_set_outover(pin_dvd_dir, GPIO_OVERRIDE_LOW);

    dvd_drv_init_pio();

    // passthrough for dstrb
    {
        uint gpclk = 0;
        if      (pin_gc_dstrb == 21) gpclk = clk_gpout0;
        else if (pin_gc_dstrb == 23) gpclk = clk_gpout1;
        else if (pin_gc_dstrb == 24) gpclk = clk_gpout2;
        else if (pin_gc_dstrb == 25) gpclk = clk_gpout3;

        clocks_hw->clk[gpclk].div = 1 << CLOCKS_CLK_GPOUT0_DIV_INT_LSB;

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    

    // gpio irq's for detecting a reset and break signal
    gpio_set_irq_enabled(pin_gc_reset, GPIO_IRQ_LEVEL_LOW, true);
    gpio_set_irq_enabled(pin_gc_brk, GPIO_IRQ_EDGE_RISE | GPIO_IRQ_EDGE_FALL, true);
    irq_set_exclusive_handler(IO_IRQ_BANK0, dvd_drv_gpio_irq);

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

    // enable pull-down to check if a physical drive is present
    gpio_set_pulls(pin_dvd_dstrb, false, true);
    sleep_us(10);

    // close cover
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
void dvd_drv_init_gpios() {
    // gpios that are always inputs
    static uint8_t inputs[] = { pin_gc_dir, pin_hstrb, pin_dvd_dstrb, pin_dvd_err, pin_dvd_cover, pin_gc_reset };
    for (int i = 0; i < sizeof(inputs); i++) {
        gpio_set_function(inputs[i], GPIO_FUNC_PIO0);
        gpio_set_oeover(inputs[i], GPIO_OVERRIDE_LOW);
        pio_sm_set_consecutive_pindirs(pio0, 0, inputs[i], 1, false);
        gpio_set_pulls(inputs[i], false, false);
    }
    gpio_set_function(pin_dvd_dstrb, GPIO_FUNC_GPCK);
    gpio_set_pulls(pin_gc_reset, true, false);

    // gpios that are always outputs
    static uint8_t outputs[] = { pin_dvd_dir, pin_gc_dstrb, pin_gc_err, pin_gc_cover, pin_dvd_reset };
    for (int i = 0; i < sizeof(outputs); i++) {
        gpio_set_function(outputs[i], GPIO_FUNC_PIO0);
        gpio_set_oeover(outputs[i], GPIO_OVERRIDE_HIGH);
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        pio_sm_config c = passthrough_program_get_default_config(offset);
        
        #define MIN4(a, b, c, d) (MIN(MIN(a, b), MIN(b, c)))
        sm_config_set_in_pins(&c, MIN4(pin_gc_dir, pin_dvd_err, pin_dvd_cover, pin_gc_reset));
        sm_config_set_out_pins(&c, MIN4(pin_dvd_dir, pin_gc_err, pin_gc_cover, pin_dvd_reset), 4);
        
        pio_sm_init(pio0, sm, offset, &c);
    }
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        sm_config_set_fifo_join(&c, PIO_FIFO_JOIN_RX);
        sm_config_set_in_shift(&c, false, true, 32);
        sm_config_set_in_pin_base(&c, pin_d0);
        sm_config_set_set_pins(&c, pin_gc_err, 1);
        sm_config_set_mov_status(&c, STATUS_RX_LESSTHAN, 3);
        pio_sm_init(pio0, sm, offset, &c);

        // store offset into y for easy reset
        pio_sm_exec(pio0, sm, pio_encode_set(pio_y, offset));

        pio_sm_set_consecutive_pindirs(pio0, sm, pin_gc_err, 1, true);
        pio_sm_exec(pio0, sm, pio_encode_set(pio_pins, 1));
    }

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        sm_config_set_out_shift(&c, true, true, 32);
        sm_config_set_out_pins(&c, pin_d0, 8);
        sm_config_set_sideset(&c, 2, true, false);
        sm_config_set_sideset_pins(&c, pin_gc_dstrb);
        pio_sm_init(pio0, sm, offset, &c);

        // store offset into y for easy reset
        pio_sm_exec(pio0, sm, pio_encode_set(pio_y, offset));

        pio_sm_set_consecutive_pindirs(pio0, sm, pin_gc_dstrb, 1, true);
    }

    // sm for changing directions of data pins
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        sm_config_set_out_pins(&c, pin_d0, 8);
        sm_config_set_out_shift(&c, false, false, 32);
        sm_config_set_sideset(&c, 2, true, false);
        sm_config_set_sideset_pins(&c, pin_gc_dstrb);
        // disable until first reset
        pio_sm_init(pio0, sm, offset + dir_offset_disable, &c);

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        // store offset+disale into x for easy disable
        pio_sm_exec(pio0, sm, pio_encode_set(pio_x, offset + dir_offset_disable));

        pio_sm_set_consecutive_pindirs(pio0, sm, pin_gc_dir, 1, false);
        pio_sm_set_consecutive_pindirs(pio0, sm, pin_d0, 8, false);
    }
}
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}

void dvd_drv_gpio_irq(void) {
    uint32_t reset_status = gpio_get_irq_event_mask(pin_gc_reset);

    // reset
    if (reset_status & GPIO_IRQ_LEVEL_LOW) {
        // force dstrb high until we are done
        gpio_set_outover(pin_gc_dstrb, GPIO_OVERRIDE_HIGH);

        // reset error
        pio_sm_exec(pio0, PIO_RECV_SM, pio_encode_set(pio_pins, 1));

        // wait for high signal next
        gpio_set_irq_enabled(pin_gc_reset, GPIO_IRQ_LEVEL_LOW, false);
        gpio_set_irq_enabled(pin_gc_reset, GPIO_IRQ_LEVEL_HIGH, true);

    } else if (reset_status & GPIO_IRQ_LEVEL_HIGH) {
        // wait for low signal next
        gpio_set_irq_enabled(pin_gc_reset, GPIO_IRQ_LEVEL_HIGH, false);
        gpio_set_irq_enabled(pin_gc_reset, GPIO_IRQ_LEVEL_LOW, true);

        // perform the reset
        dvd_drv_clear_state();
        dvd_reset();

        // release dstrb
        gpio_set_outover(pin_gc_dstrb, GPIO_OVERRIDE_NORMAL);
    }

    uint32_t brk_status = gpio_get_irq_event_mask(pin_gc_brk);
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}

void dvd_drv_set_cover(bool open) {
    gpio_set_outover(pin_gc_cover, open ? GPIO_OVERRIDE_HIGH : GPIO_OVERRIDE_LOW);
}

bool dvd_drv_enable_passthrough()
{
    // only activate passthrough if a drive is present
    if (!gpio_get(pin_dvd_dstrb))
        return false;
    gpio_set_pulls(pin_dvd_dstrb, false, false);

    irq_set_enabled(IO_IRQ_BANK0, false);
    irq_set_enabled(PIO0_IRQ_0, false);
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    pio_sm_set_enabled(pio0, PIO_RECV_SM, false);

    pio_sm_set_enabled(pio0, PIO_PASSTHROUGH_SM, true);
    gpio_set_function(pin_gc_dstrb, GPIO_FUNC_GPCK);

    gpio_set_outover(pin_dvd_dir, GPIO_OVERRIDE_NORMAL);
    gpio_set_outover(pin_gc_cover, GPIO_OVERRIDE_NORMAL);
    gpio_set_outover(pin_dvd_reset, GPIO_OVERRIDE_NORMAL);

    return true;
}
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
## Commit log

2025-06-29 initial code commit
2025-06-29 code cleanup and break pin test
2025-06-29 uf2 payload
2025-06-30 task function placeholder and code cleanup
2025-06-30 valid payload check
2025-06-30 updated gitignore
2025-06-30 missing build file
2025-06-30 native dol support
2025-07-01 updated generic boot image
2025-07-01 removed debug code
2025-07-01 limit read to flash
2025-07-16 custom command to reboot into bootloader
2025-07-16 drive presence check
2025-07-18 region free gbi.hdr
2025-07-20 gbi with boot animation
2025-07-22 fixed swiss crash using dol
2025-07-25 add basic info/usage on PicoLoader
2025-07-25 added flex kicad project
    Interposer flex for PicoLoader
2025-07-25 added solder flex kicad project
    PicoLoader mobo solderflex option
2025-07-25 flex mount stls
2025-07-25 interposer flex pics
2025-07-25 solderflex pics
2025-07-26 updated silkscreen
2025-07-26 update silkscreen images
2025-07-26 status led
2025-07-28 web uf2 converter
2025-07-29 discord link
2025-07-29 restructuring
2025-07-29 folder rename
2025-07-29 cleanup
2025-07-30 improvement in case of no payload and no drive
2025-07-30 check if dol is bootable by ipl
2025-07-31 add mount with screw holder
2025-07-31 Delete mount/Interposer_Mount_v1.4.stl
    removing old mount without screw holder
2025-07-31 text adjustments
2025-07-31 gerber rename
2025-07-31 text clarification
2025-08-01 version info in device info
2025-08-01 converter now includes firmware
2025-08-01 workaround for CORS
2025-08-01 Create action for release upload
2025-08-01 rename of workflow
2025-08-01 use correct branch
2025-08-01 manual trigger
2025-08-01 Update fw files to
2025-08-01 removed manual trigger
2025-08-01 always copy latest release to pages
2025-08-01 removed broken fw
2025-08-01 Update fw files to latest release null
2025-08-01 workflow debug echo
2025-08-01 workflow debugging
2025-08-01 more workflow debugging
2025-08-01 fixed bad commit message
2025-08-01 testing alt auth header
2025-08-02 fixed workflow download
2025-08-02 workflow cleanup
2025-08-02 readme pictures
2025-08-02 changed inquiry response
2025-08-02 removed "no overdriving" feature
2025-08-02 missing acknowledgements for apploader
2025-08-02 fixed typo
2025-08-02 removed old apploader
2025-08-03 apploader now holds drive in reset on exit
2025-08-03 bump version to v1.1
2025-08-04 OneBoard v1.0 RC1
2025-08-04 PCB Attribution Update
    - added explicit attribution to silverstone
2025-08-04 Fix silversteel's name
    - This is why I shouldn't be working on projects past 1am
2025-08-04 installation disclaimer
2025-08-04 fixed typo in readme
2025-08-04 link to installation instructions
2025-08-08 improved scaling on small screens
2025-08-10 donation link
2025-08-18 Update board per suggested changes
    - Replace components with JLCPCB basic components where possible
    - Implement Red LED for GPIO25
    - Adjust revision to Rev1.0
2025-08-18 27ohm -> 22 ohm for USB resistors
2025-08-23 gerber example order images
    sample images on how what settings to have selected to order gerbers
2025-08-30 getting started page
2025-08-30 fixed link to installation guide
2025-08-30 open link in same tab
2025-08-30 fixed title
2025-08-30 make images not clickable
    Updated gallery section to make images clickable links.
2025-08-30 image for solderless install
2025-08-30 style improvement
2025-08-30 solderless overlay
2025-08-31 link to install instructions selection
2025-08-31 update links to instructions
2025-08-31 update solderless image
2025-08-31 solderless galery images
    Added additional images to the README for better visualization.
2025-08-31 change license to GPL-2.0
2025-09-01 pico 2 support
2025-09-01 updated apploader
2025-09-01 update pico sdk
2025-09-01 bump version to v1.2
2025-09-02 remove dead code
2025-09-02 fix rp2350 family id
2025-09-02 remove cursed uf2 block for rp2350
2025-09-02 readme pico 2
    Updated component list to include Raspberry Pi Pico 2.
2025-09-14 added Panasonic Q flex gerbers and kicad project
2025-09-14 mount for Panasonic Q Flex
2025-09-14 Panasonic Q restructure
2025-09-14 Panasonic Q readme changes
2025-09-15 uf2 merge tool
2025-09-15 license file
2025-09-18 improve compatibility with slow starting crystals
2025-09-19 bump version to v1.3
2025-09-22 list solderless variant in readme
2025-09-24 DVD Plug stl for driveless flex use
2025-09-24 rename dvd plug
2025-09-24 mention drive plug in readme
2025-10-09 mention sd adapters
2025-10-16 update shipping info
    Removed note about shipping restrictions to the USA.
2025-10-21 change apploader repo
2025-10-21 apploader for gekkoboot
2025-10-21 ignore sram if ipl disabled
2025-11-24 feat: repo-breaking spelling error caught and fixed before it was too late
2025-12-01 fold key stl
2026-01-28 solderless module files
